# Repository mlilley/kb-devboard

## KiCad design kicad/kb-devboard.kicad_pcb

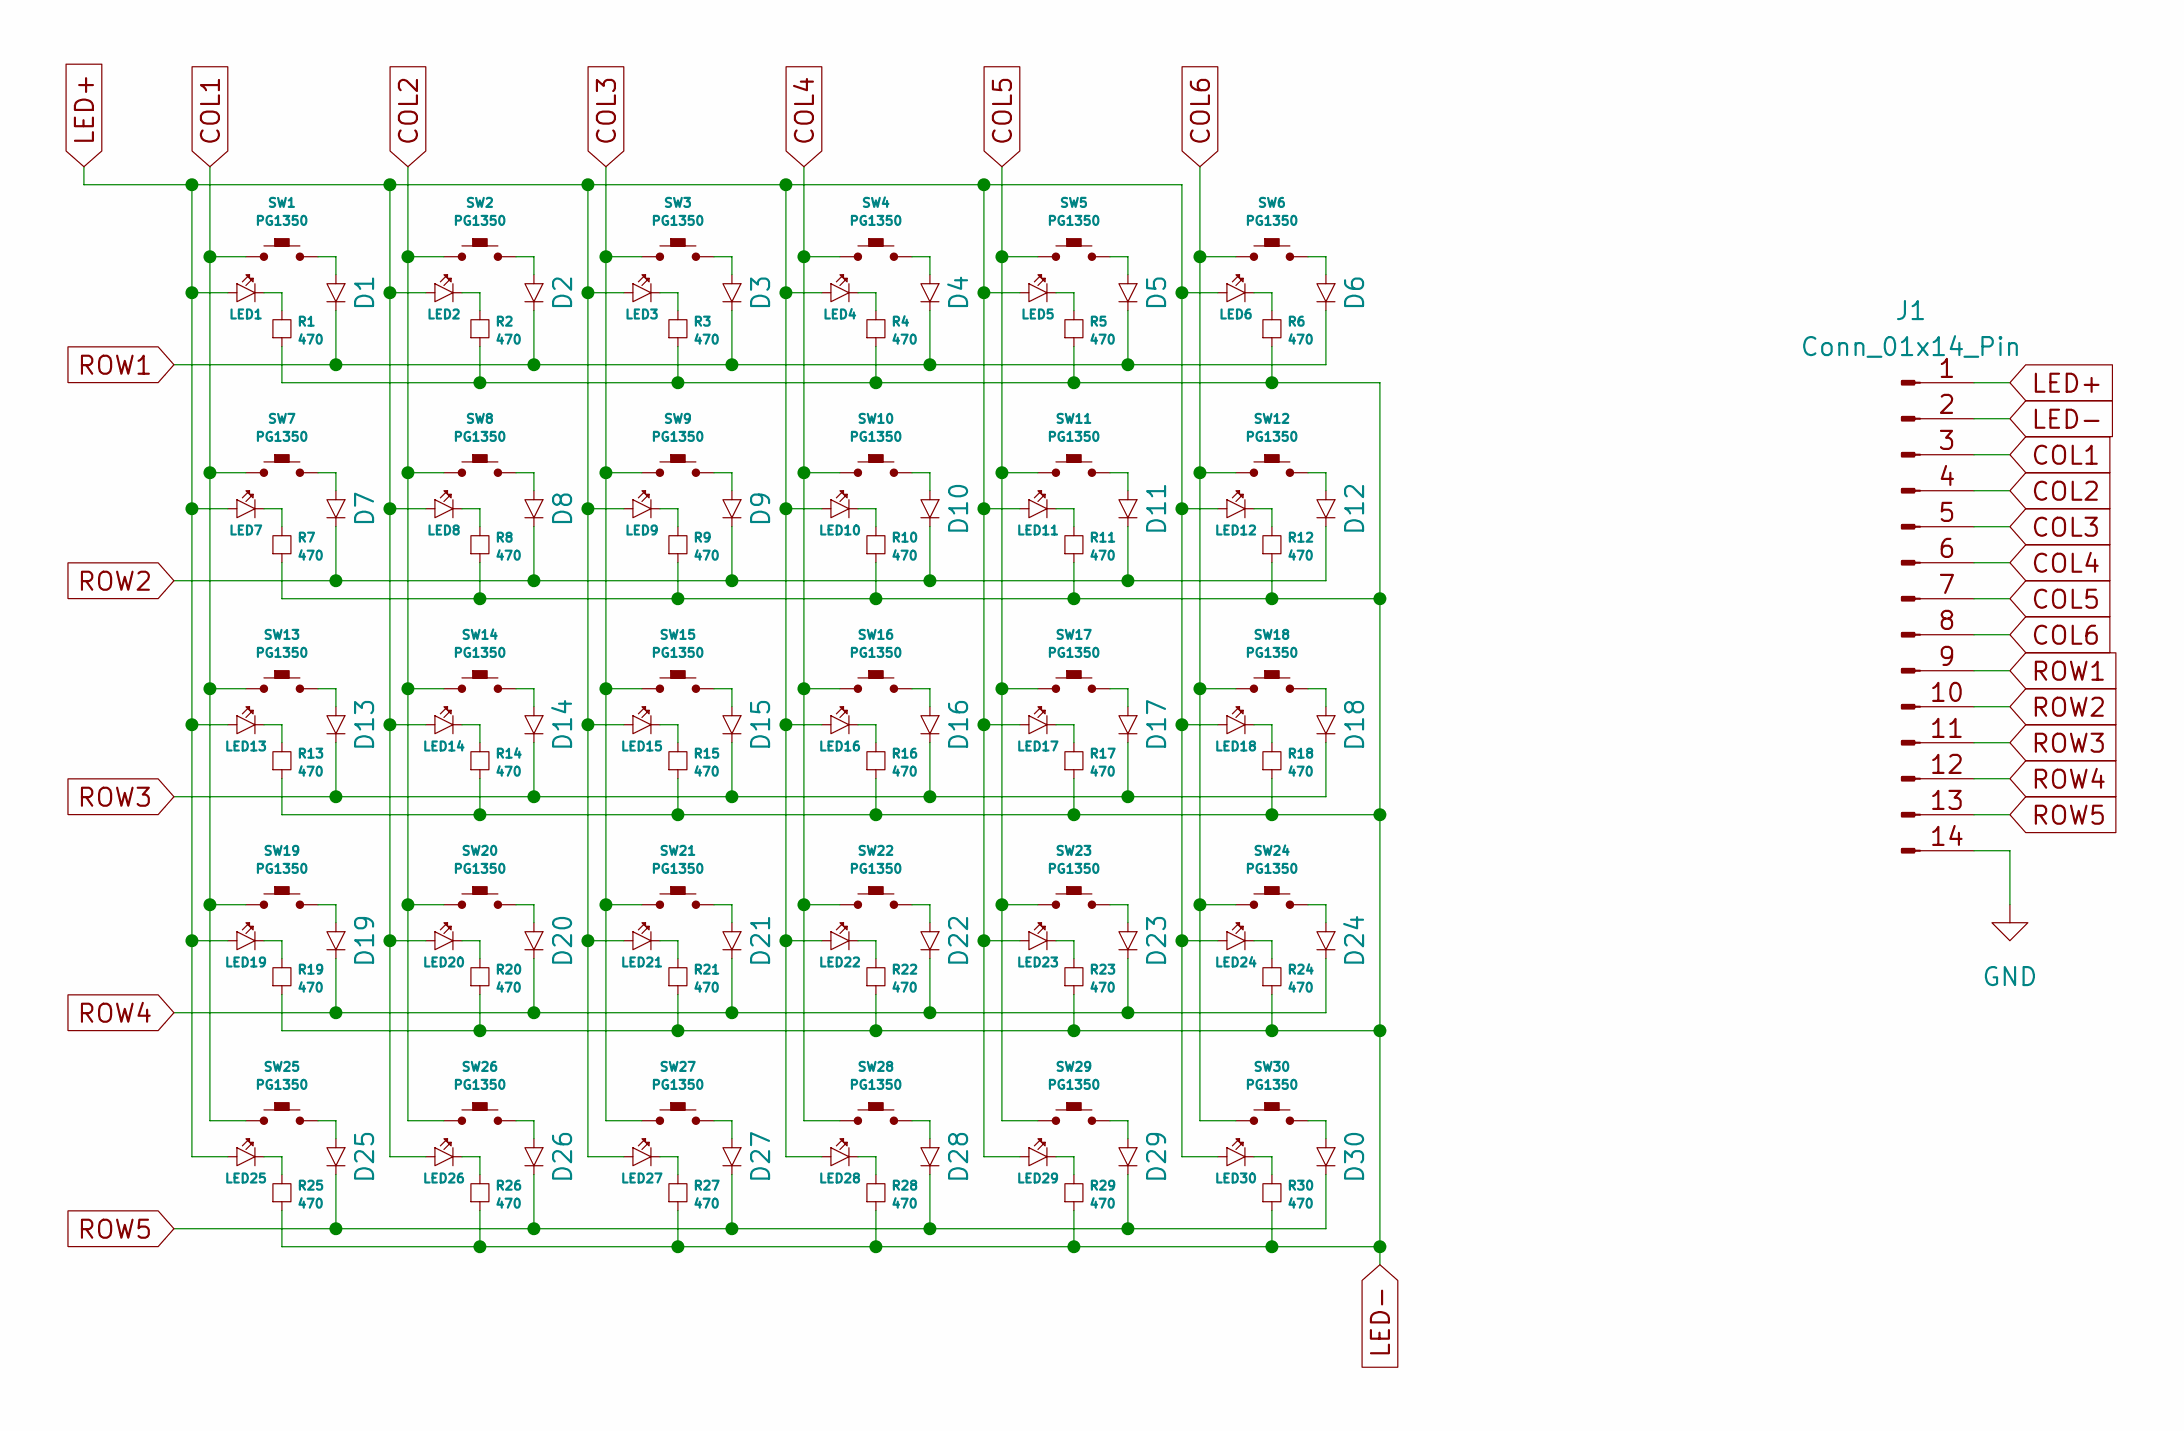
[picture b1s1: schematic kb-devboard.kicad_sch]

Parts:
D1, D2, D3, D4, D5, D6, D7, D8, D9, D10, D11, D12, D13, D14, D15, D16, D17, D18, D19, D20, D21, D22, D23, D24, D25, D26, D27, D28, D29, D30: D_SOD-123
J1: Conn_01x14_Pin; PinHeader_1x14_P2.54mm_Vertical
LED1, LED2, LED3, LED4, LED5, LED6, LED7, LED8, LED9, LED10, LED11, LED12, LED13, LED14, LED15, LED16, LED17, LED18, LED19, LED20, LED21, LED22, LED23, LED24, LED25, LED26, LED27, LED28, LED29, LED30: LED_1206_3216Metric_Pad1.42x1.75mm_HandSolder
R1, R2, R3, R4, R5, R6, R7, R8, R9, R10, R11, R12, R13, R14, R15, R16, R17, R18, R19, R20, R21, R22, R23, R24, R25, R26, R27, R28, R29, R30: 470; R_1206_3216Metric_Pad1.30x1.75mm_HandSolder
SW1, SW2, SW3, SW4, SW5, SW6, SW7, SW8, SW9, SW10, SW11, SW12, SW13, SW14, SW15, SW16, SW17, SW18, SW19, SW20, SW21, SW22, SW23, SW24, SW25, SW26, SW27, SW28, SW29, SW30: PG1350; pg1350-HCN

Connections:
COL1: J1.3, SW1.1, SW7.1, SW13.1, SW19.1, SW25.1
COL2: J1.4, SW2.1, SW8.1, SW14.1, SW20.1, SW26.1
COL3: J1.5, SW3.1, SW9.1, SW15.1, SW21.1, SW27.1
COL4: J1.6, SW4.1, SW10.1, SW16.1, SW22.1, SW28.1
COL5: J1.7, SW5.1, SW11.1, SW17.1, SW23.1, SW29.1
COL6: J1.8, SW6.1, SW12.1, SW18.1, SW24.1, SW30.1
GND: J1.14
LED+: J1.1, LED1.1 (A), LED2.1 (A), LED3.1 (A), LED4.1 (A), LED5.1 (A), LED6.1 (A), LED7.1 (A), LED8.1 (A), LED9.1 (A), LED10.1 (A), LED11.1 (A), LED12.1 (A), LED13.1 (A), LED14.1 (A), LED15.1 (A), LED16.1 (A), LED17.1 (A), LED18.1 (A), LED19.1 (A), LED20.1 (A), LED21.1 (A), LED22.1 (A), LED23.1 (A), LED24.1 (A), LED25.1 (A), LED26.1 (A), LED27.1 (A), LED28.1 (A), LED29.1 (A), LED30.1 (A)
LED-: J1.2, R1.1, R2.1, R3.1, R4.1, R5.1, R6.1, R7.1, R8.1, R9.1, R10.1, R11.1, R12.1, R13.1, R14.1, R15.1, R16.1, R17.1, R18.1, R19.1, R20.1, R21.1, R22.1, R23.1, R24.1, R25.1, R26.1, R27.1, R28.1, R29.1, R30.1
unnamed: D1.2, SW1.2
unnamed: D2.2, SW2.2
unnamed: D3.2, SW3.2
unnamed: D4.2, SW4.2
unnamed: D5.2, SW5.2
unnamed: D6.2, SW6.2
unnamed: D7.2, SW7.2
unnamed: D8.2, SW8.2
unnamed: D9.2, SW9.2
unnamed: D10.2, SW10.2
unnamed: D11.2, SW11.2
unnamed: D12.2, SW12.2
unnamed: D13.2, SW13.2
unnamed: D14.2, SW14.2
unnamed: D15.2, SW15.2
unnamed: D16.2, SW16.2
unnamed: D17.2, SW17.2
unnamed: D18.2, SW18.2
unnamed: D19.2, SW19.2
unnamed: D20.2, SW20.2
unnamed: D21.2, SW21.2
unnamed: D22.2, SW22.2
unnamed: D23.2, SW23.2
unnamed: D24.2, SW24.2
unnamed: D25.2, SW25.2
unnamed: D26.2, SW26.2
unnamed: D27.2, SW27.2
unnamed: D28.2, SW28.2
unnamed: D29.2, SW29.2
unnamed: D30.2, SW30.2
unnamed: LED1.2 (K), R1.2
unnamed: LED2.2 (K), R2.2
unnamed: LED3.2 (K), R3.2
unnamed: LED4.2 (K), R4.2
unnamed: LED5.2 (K), R5.2
unnamed: LED6.2 (K), R6.2
unnamed: LED7.2 (K), R7.2
unnamed: LED8.2 (K), R8.2
unnamed: LED9.2 (K), R9.2
unnamed: LED10.2 (K), R10.2
unnamed: LED11.2 (K), R11.2
unnamed: LED12.2 (K), R12.2
unnamed: LED13.2 (K), R13.2
unnamed: LED14.2 (K), R14.2
unnamed: LED15.2 (K), R15.2
unnamed: LED16.2 (K), R16.2
unnamed: LED17.2 (K), R17.2
unnamed: LED18.2 (K), R18.2
unnamed: LED19.2 (K), R19.2
unnamed: LED20.2 (K), R20.2
unnamed: LED21.2 (K), R21.2
unnamed: LED22.2 (K), R22.2
unnamed: LED23.2 (K), R23.2
unnamed: LED24.2 (K), R24.2
unnamed: LED25.2 (K), R25.2
unnamed: LED26.2 (K), R26.2
unnamed: LED27.2 (K), R27.2
unnamed: LED28.2 (K), R28.2
unnamed: LED29.2 (K), R29.2
unnamed: LED30.2 (K), R30.2
ROW1: D1.1, D2.1, D3.1, D4.1, D5.1, D6.1, J1.9
ROW2: D7.1, D8.1, D9.1, D10.1, D11.1, D12.1, J1.10
ROW3: D13.1, D14.1, D15.1, D16.1, D17.1, D18.1, J1.11
ROW4: D19.1, D20.1, D21.1, D22.1, D23.1, D24.1, J1.12
ROW5: D25.1, D26.1, D27.1, D28.1, D29.1, D30.1, J1.13

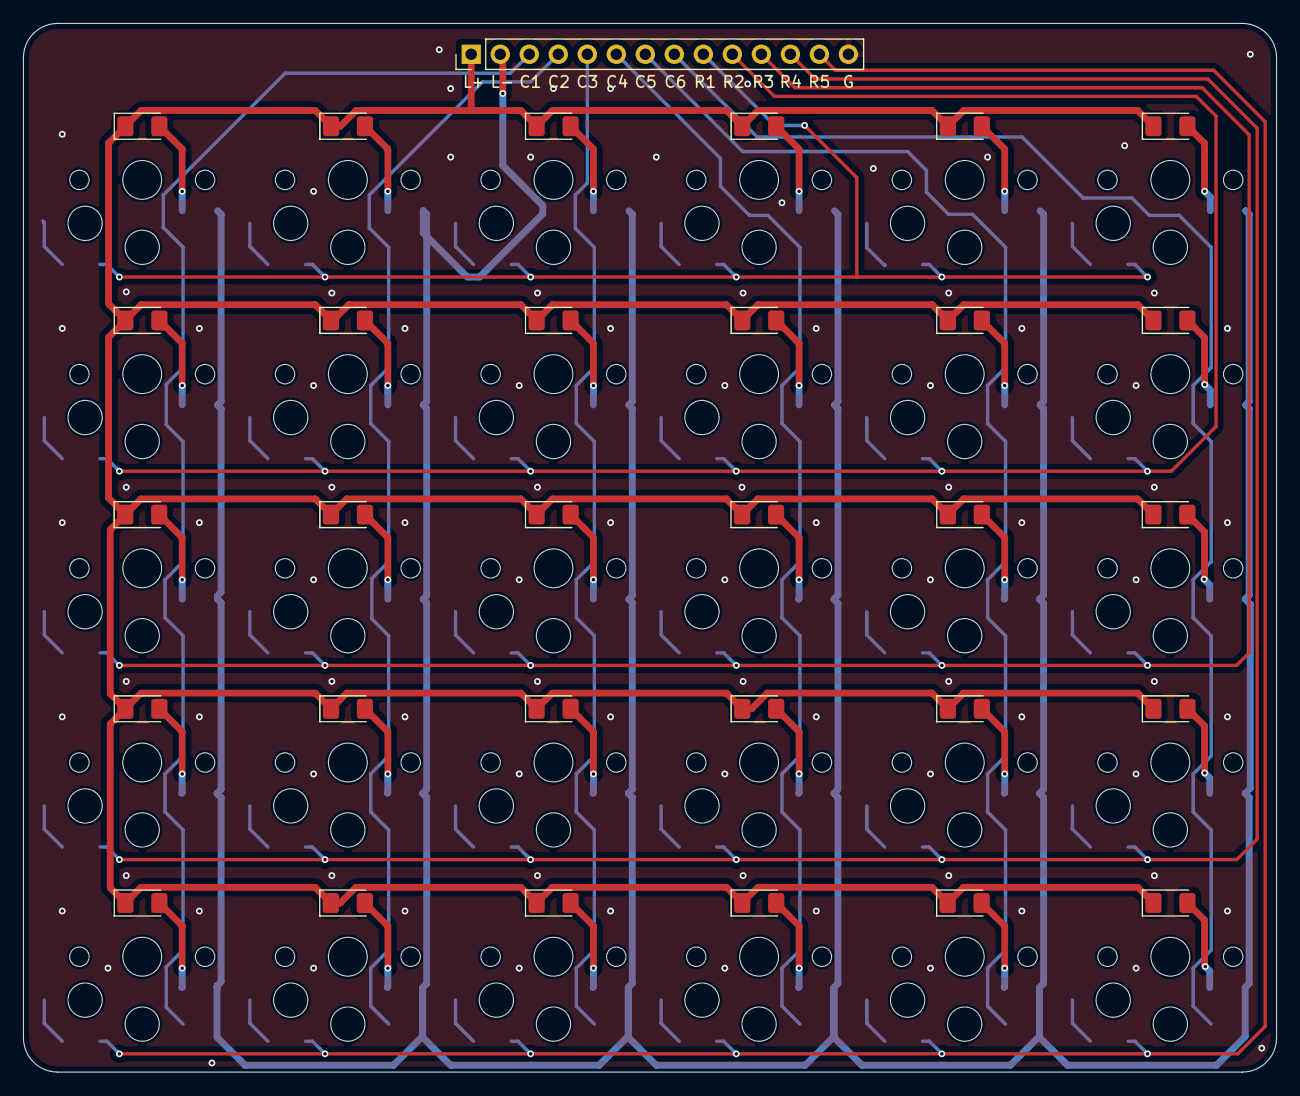
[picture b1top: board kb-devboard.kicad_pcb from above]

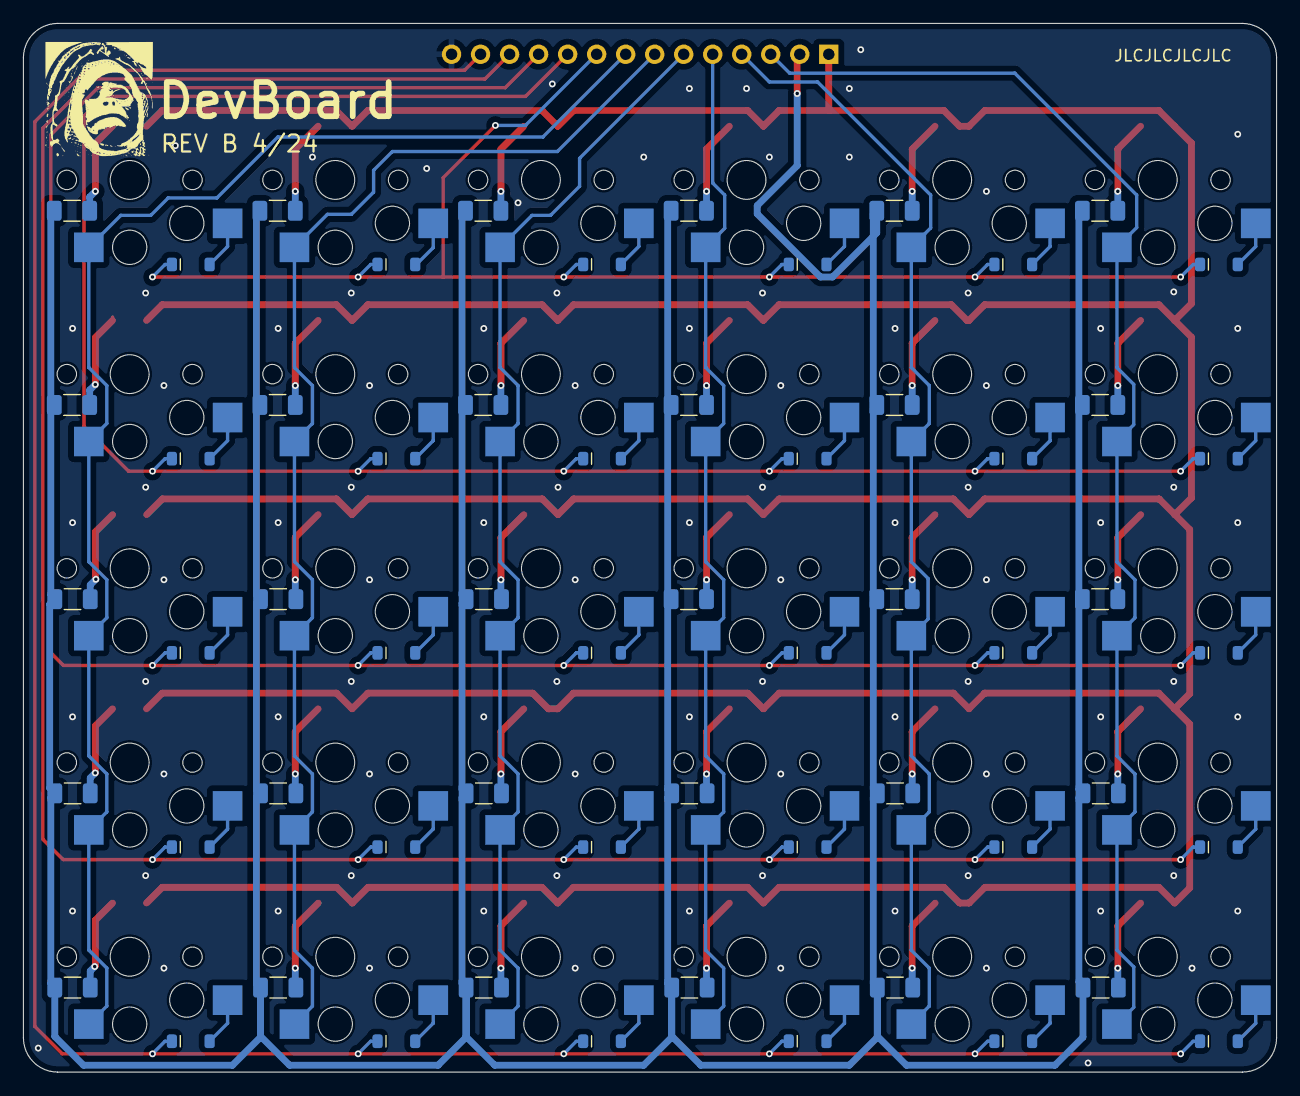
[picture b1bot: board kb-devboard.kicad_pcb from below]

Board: 2 copper layers, 109.7 x 91.8 mm, 121 parts (60 on the bottom side), 73 nets.

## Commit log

2024-03-09 Initial
2024-03-09 Fix ignore
2024-03-09 Readme
2024-03-09 Schematic bg
2024-03-10 Improved routing
2024-03-10 Update imgs
2024-03-10 Logo
2024-03-10 Update back img
2024-03-10 Add production
2024-03-10 Fix ignore production
2024-04-10 Keypad with leds, without logic
2024-04-10 Update to rev b
